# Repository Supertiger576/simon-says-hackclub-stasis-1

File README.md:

# simon-says-hackclub-stasis
My version of the Pathfinder for Hack Club Stasis
A PCB with 4 buttons and 4 LEDS.    
After holding one of the buttons for 3 seconds you can initiate a simon says game   <br/>
KiCAD render:   <br />

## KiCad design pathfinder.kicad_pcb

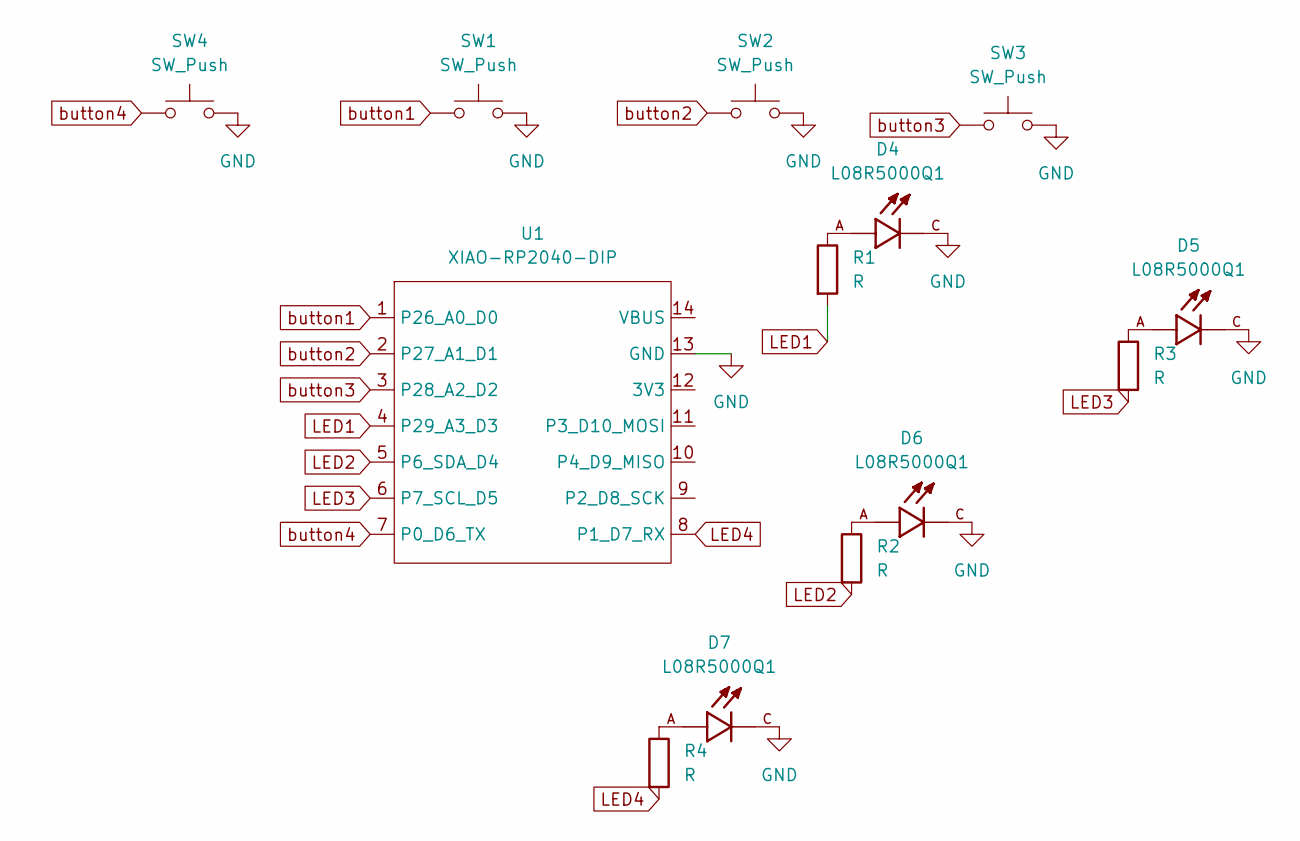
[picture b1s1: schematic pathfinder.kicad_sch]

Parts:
D4, D5, D6, D7: L08R5000Q1; LEDRD254W57D500H1070; PARTREV NA
R1, R2, R3, R4: R; R_Axial_DIN0204_L3.6mm_D1.6mm_P5.08mm_Horizontal
SW1, SW2, SW3, SW4: SW_Push; SW_Cherry_MX_1.00u_PCB
U1: XIAO-RP2040-DIP

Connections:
GND: D4.C, D5.C, D6.C, D7.C, SW1.2, SW2.2, SW3.2, SW4.2, U1.13 (GND)
LED1: R1.2, U1.4 (P29_A3_D3)
LED2: R2.2, U1.5 (P6_SDA_D4)
LED3: R3.2, U1.6 (P7_SCL_D5)
LED4: R4.2, U1.8 (P1_D7_RX)
unnamed: D4.A, R1.1
unnamed: D5.A, R3.1
unnamed: D6.A, R2.1
unnamed: D7.A, R4.1
button1: SW1.1, U1.1 (P26_A0_D0)
button2: SW2.1, U1.2 (P27_A1_D1)
button3: SW3.1, U1.3 (P28_A2_D2)
button4: SW4.1, U1.7 (P0_D6_TX)

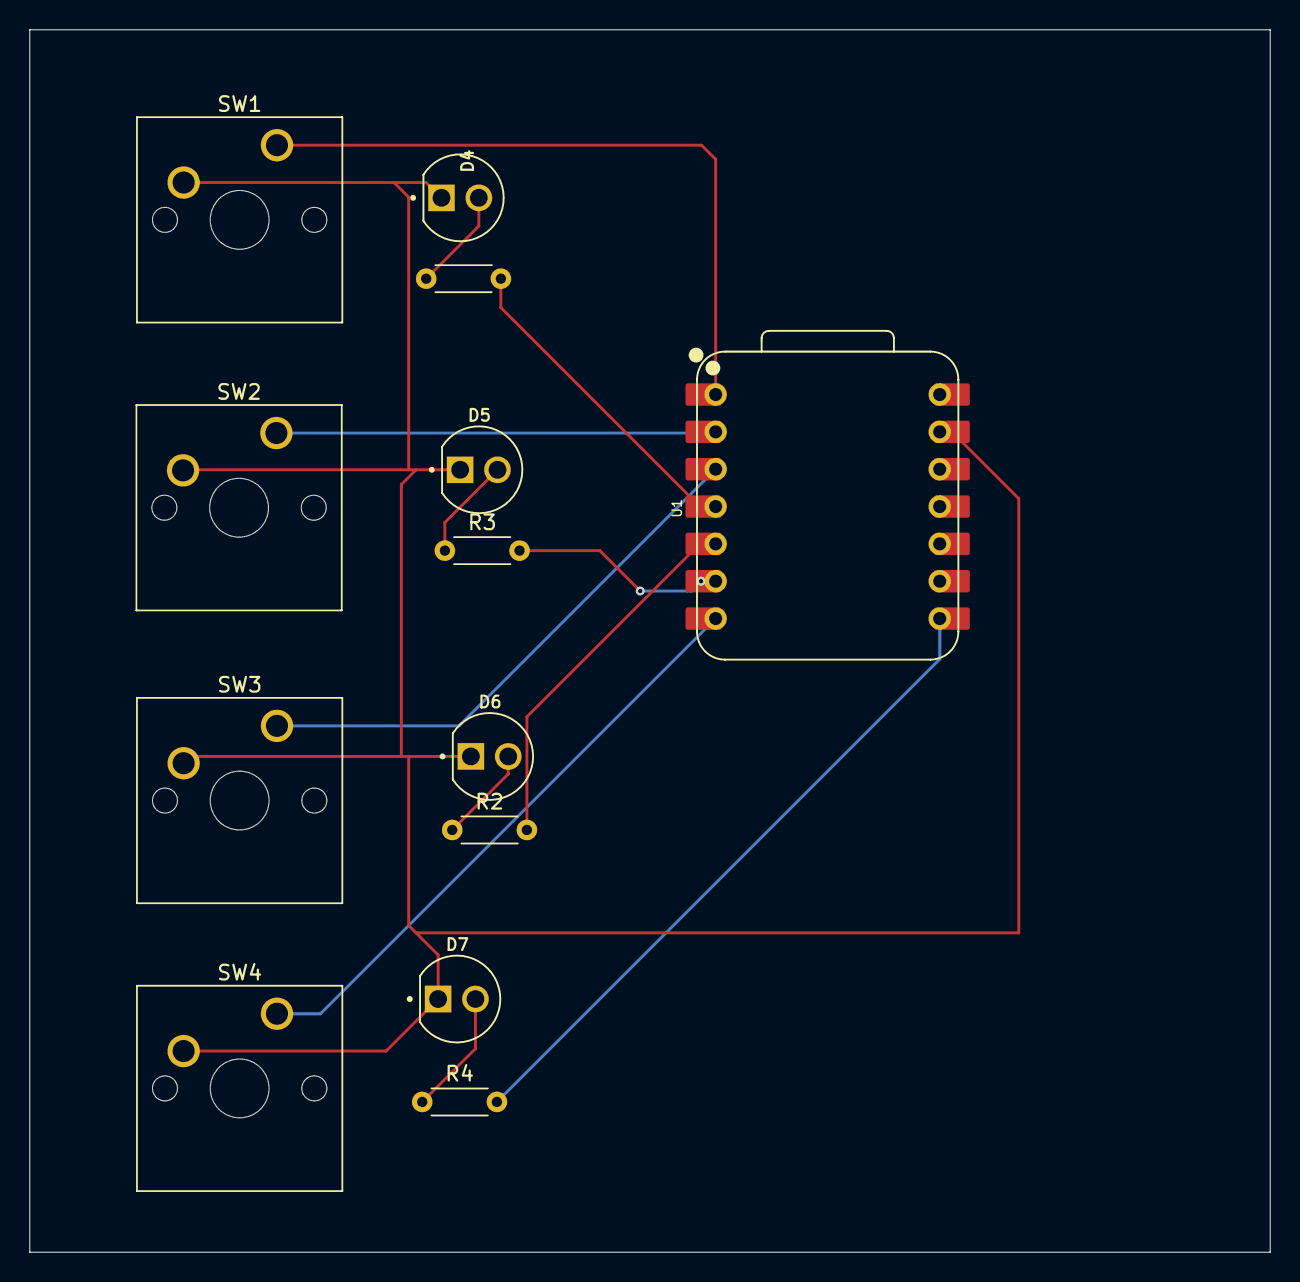
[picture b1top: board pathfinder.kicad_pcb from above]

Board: 2 copper layers, 84.4 x 83.2 mm, 13 parts (0 on the bottom side), 13 nets.

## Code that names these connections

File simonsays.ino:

// might not work yet
int button1 = D0;
int button2 = D1;
int button3 = D2;
int button4 = D8;
int LED1 = D3;
int LED2 = D4;
int LED3 = D5;
int LED4 = D7;
int numberslist[100];
int numberslistlength = 0;
bool failed = false;
void setup() {

pinMode(button1, INPUT_PULLUP);
pinMode(button2, INPUT_PULLUP);
pinMode(button3, INPUT_PULLUP);
pinMode(button4, INPUT_PULLUP);
pinMode(LED1, OUTPUT);
pinMode(LED2, OUTPUT);
pinMode(LED3, OUTPUT);
pinMode(LED4, OUTPUT);
randomSeed(analogRead(A0));

}

void loop() {
    if (digitalRead(button1) == LOW) {
        delay(3000);
        if (digitalRead(button1) == LOW) {
            while(digitalRead(button1) == LOW) {
                1+1;
            }
            while(true) {
                if(failed){
                    numberslistlength = 0;
                    failed = false;
                    break;
                }
                if (numberslistlength >= 99) {
                    digitalWrite(LED1,HIGH);
                    digitalWrite(LED2,HIGH);
                    digitalWrite(LED3,HIGH);
                    digitalWrite(LED4,HIGH);
                    delay(10000);
                    break;
                }
                    int r = random(1, 5);
                    numberslist[numberslistlength] = r;
                    numberslistlength +=1;
                    for (int i=0; i<numberslistlength; i++) {

                        if ((numberslist[i]) == 1) {
                            digitalWrite(LED1,HIGH);
                            delay(500);
                            digitalWrite(LED1,LOW);
                        }
                        else if ((numberslist[i]) == 2) {
                            digitalWrite(LED2,HIGH);
                            delay(500);
                            digitalWrite(LED2,LOW);
                        }
                        else if ((numberslist[i]) == 3) {
                            digitalWrite(LED3,HIGH);
                            delay(500);
                            digitalWrite(LED3,LOW);
                        }
                        else if ((numberslist[i]) == 4) {
                            digitalWrite(LED4,HIGH);
                            delay(500);
                            digitalWrite(LED4,LOW);
                        }
                    delay(100);
                    }
                    delay(100);
                        if(failed){
                            numberslistlength = 0;
                            failed = false;
                            break;
                        }
                        for (int i=0; i<numberslistlength; i++) {
                            while(digitalRead(button1)==HIGH && digitalRead(button2)==HIGH && digitalRead(button3)==HIGH && digitalRead(button4)==HIGH){
                                1+1;
                            }
                            if(digitalRead(button1) == LOW) {
                                if (numberslist[i] == 1) {
                                    while(digitalRead(button1) == LOW) {
                                        1+1;
                                    }
                                }
                                else {
                                    failed = true;
                                    break;
                                }
                            }
                            else if(digitalRead(button2) == LOW) {
                                if (numberslist[i] == 2) {
                                    while(digitalRead(button2) == LOW) {
                                        1+1;
                                    }
                                }
                                else {
                                    failed = true;
                                    break;
                                }
                            }
                            else if(digitalRead(button3) == LOW) {
                                if (numberslist[i] == 3) {
                                    while(digitalRead(button3) == LOW) {
                                        1+1;
                                    }
                                }
                                else {
                                    failed = true;
                                    break;      
                                }
                            }
                            else if(digitalRead(button4) == LOW) {
                                if (numberslist[i] == 4 ){
                                    while(digitalRead(button4) == LOW) {
                                        1+1;
                                    }
                                }
                                else {
                                    failed = true;
                                    break;
                                }
        
                            }
                        } 
                        
                    }
                }
            }
        }

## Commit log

2026-04-10 Add files via upload
    auto created by kicad wrong one
